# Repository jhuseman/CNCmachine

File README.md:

# CNCmachine

This is an ongoing experimental project to create a CNC mill using a Raspberry Pi and Arduino microcontroller for control, 
along with 3D-printed parts for the mechanical motion, rather than more expensive, precisely machined parts and expensive hardware for the control software.

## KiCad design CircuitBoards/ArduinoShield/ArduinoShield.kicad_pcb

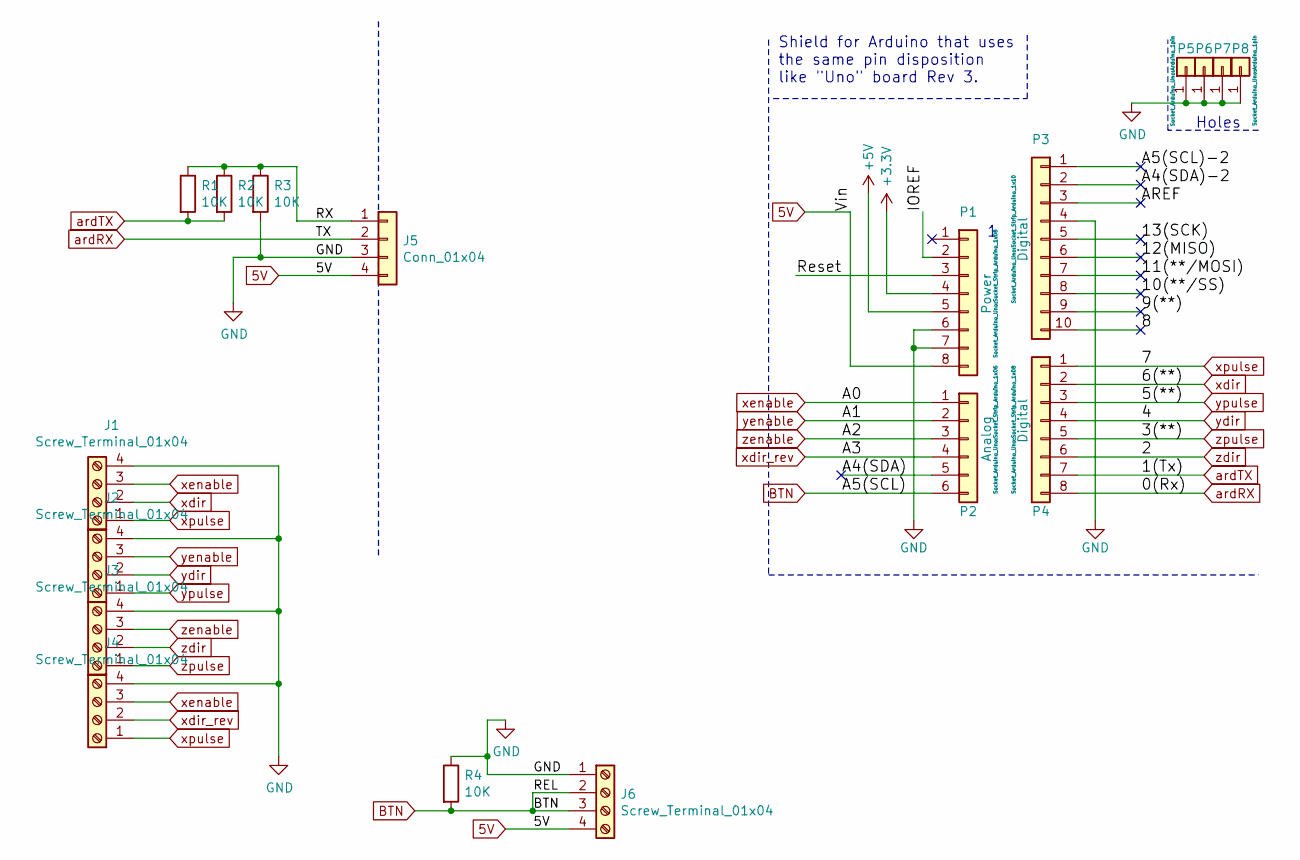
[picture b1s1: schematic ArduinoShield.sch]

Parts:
J1, J2, J3, J4, J6: Screw_Terminal_01x04; TerminalBlock_MetzConnect_Type011_RT05504HBWC_1x04_P5.00mm_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
J5: Conn_01x04; PinSocket_1x04_P2.54mm_Vertical
P1: Power; Socket_Strip_Arduino_1x08
P2: Analog; Socket_Strip_Arduino_1x06
P3: Digital; Socket_Strip_Arduino_1x10
P4: Digital; Socket_Strip_Arduino_1x08
P5, P6, P7, P8: CONN_01X01; Arduino_1pin
R1, R2, R3, R4: 10K; R_Axial_DIN0204_L3.6mm_D1.6mm_P7.62mm_Horizontal

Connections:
5V: J5.4, J6.4, P1.8
+3V3: P1.4
+5V: P1.5
/8: P3.10
/9(**): P3.9
/10(**/SS): P3.8
/11(**/MOSI): P3.7
/12(MISO): P3.6
/13(SCK): P3.5
/A4(SDA): P2.5
/A4(SDA)-2: P3.2
/A5(SCL)-2: P3.1
/AREF: P3.3
/IOREF: P1.2
/RX: J5.1, R1.1, R2.1, R3.1
/Reset: P1.3
BTN: J6.2, J6.3, P2.6, R4.2
GND: J1.4, J2.4, J3.4, J4.4, J5.3, J6.1, P1.6, P1.7, P3.4, P5.1, P6.1, P7.1, P8.1, R3.2, R4.1
ardRX: J5.2, P4.8
ardTX: P4.7, R1.2, R2.2
xdir: J1.2, P4.2
xdir_rev: J4.2, P2.4
xenable: J1.3, J4.3, P2.1
xpulse: J1.1, J4.1, P4.1
ydir: J2.2, P4.4
yenable: J2.3, P2.2
ypulse: J2.1, P4.3
zdir: J3.2, P4.6
zenable: J3.3, P2.3
zpulse: J3.1, P4.5

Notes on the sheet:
Shield for Arduino that uses the same pin disposition like "Uno" board Rev 3.
Holes

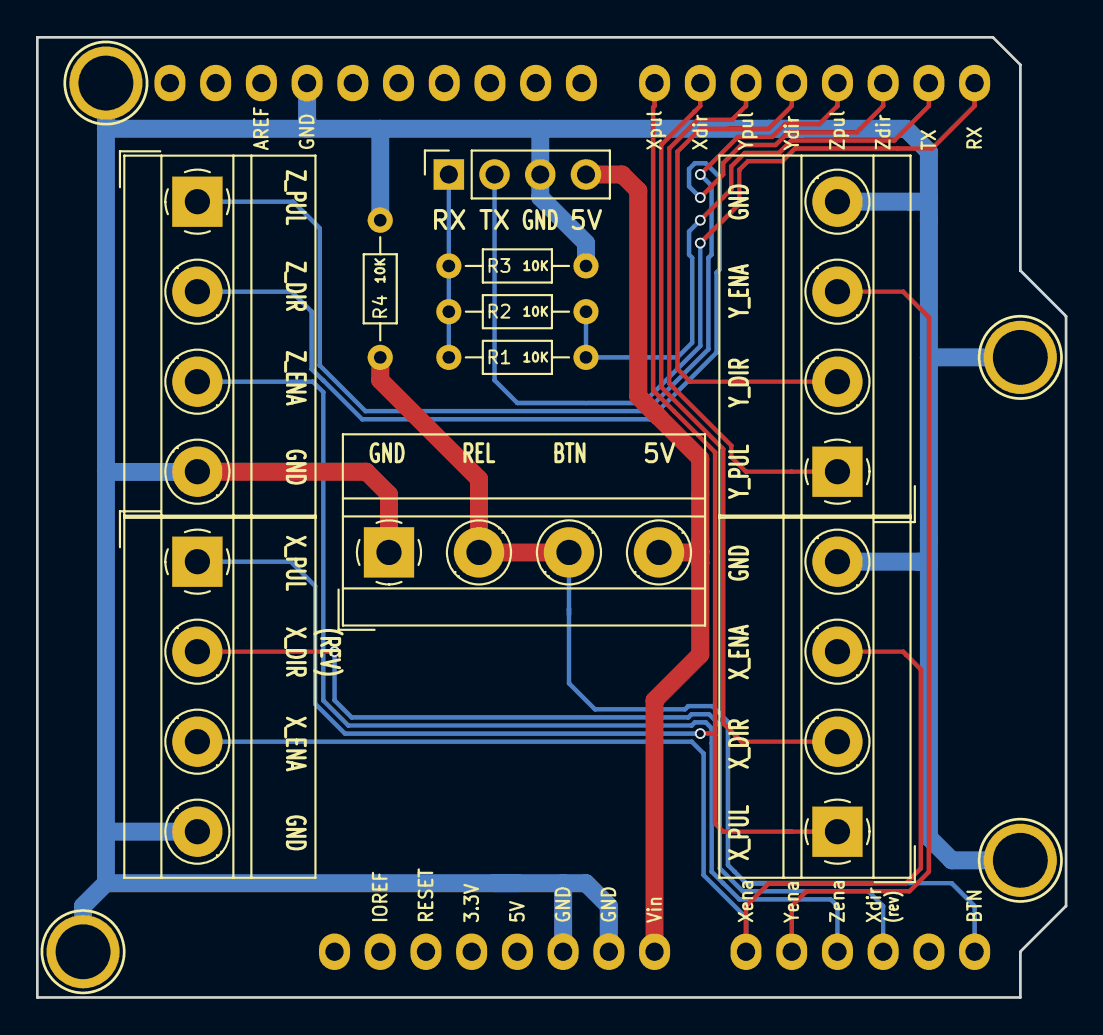
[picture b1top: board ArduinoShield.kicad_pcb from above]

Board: 2 copper layers, 57.2 x 53.3 mm, 18 parts (0 on the bottom side), 16 nets.

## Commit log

2019-01-03 Add all source Code
2019-01-03 Made all python files executable
2019-01-03 Updated identifier used for serial port on PI
2019-01-04 created partial setup script
2019-01-04 updated requirements.txt
2019-01-04 removed unnecessary import
2019-01-04 Added explicit UTF-8 encoding, for python3 upgrade.
2019-01-04 Modify setup script to work with python3
2019-01-04 Update method of encoding in utf-8 to prevent error on other write() methods
2019-01-04 bug fix
2019-01-04 fixed encoding/decoding bug (hopefully)
2019-01-04 Added debug message
2019-01-04 changed debug message
2019-01-04 removed debug prints
2019-01-04 Bug fix in movement_step, added test code.
2019-01-04 debug test prints
2019-01-04 Fixed bug causing incorrect position tracking (hopefully)
2019-01-04 Removed some debug prints
2019-01-04 Added code to handle repeated G-codes on the same line without losing the corresponding numbers
2019-01-04 Removed TODO marking that is no longer relevant.
2019-01-04 Added multi_stream and tee_stream to split messages to both display on the console and send them to the arduino.
2019-01-04 Switched to using tee for output stream, instead of multi_stream.
2019-01-25 Refactored arduino code to use several classes in various files instead of one mega-file. Designed PCB for Arduino Shield
2019-01-25 Refactored to convert handle_command function into CommandHandler class.
2019-02-11 Moved python files inside separate directory.
2019-03-08 Update README.md
    Add description of the purpose of the repository.
